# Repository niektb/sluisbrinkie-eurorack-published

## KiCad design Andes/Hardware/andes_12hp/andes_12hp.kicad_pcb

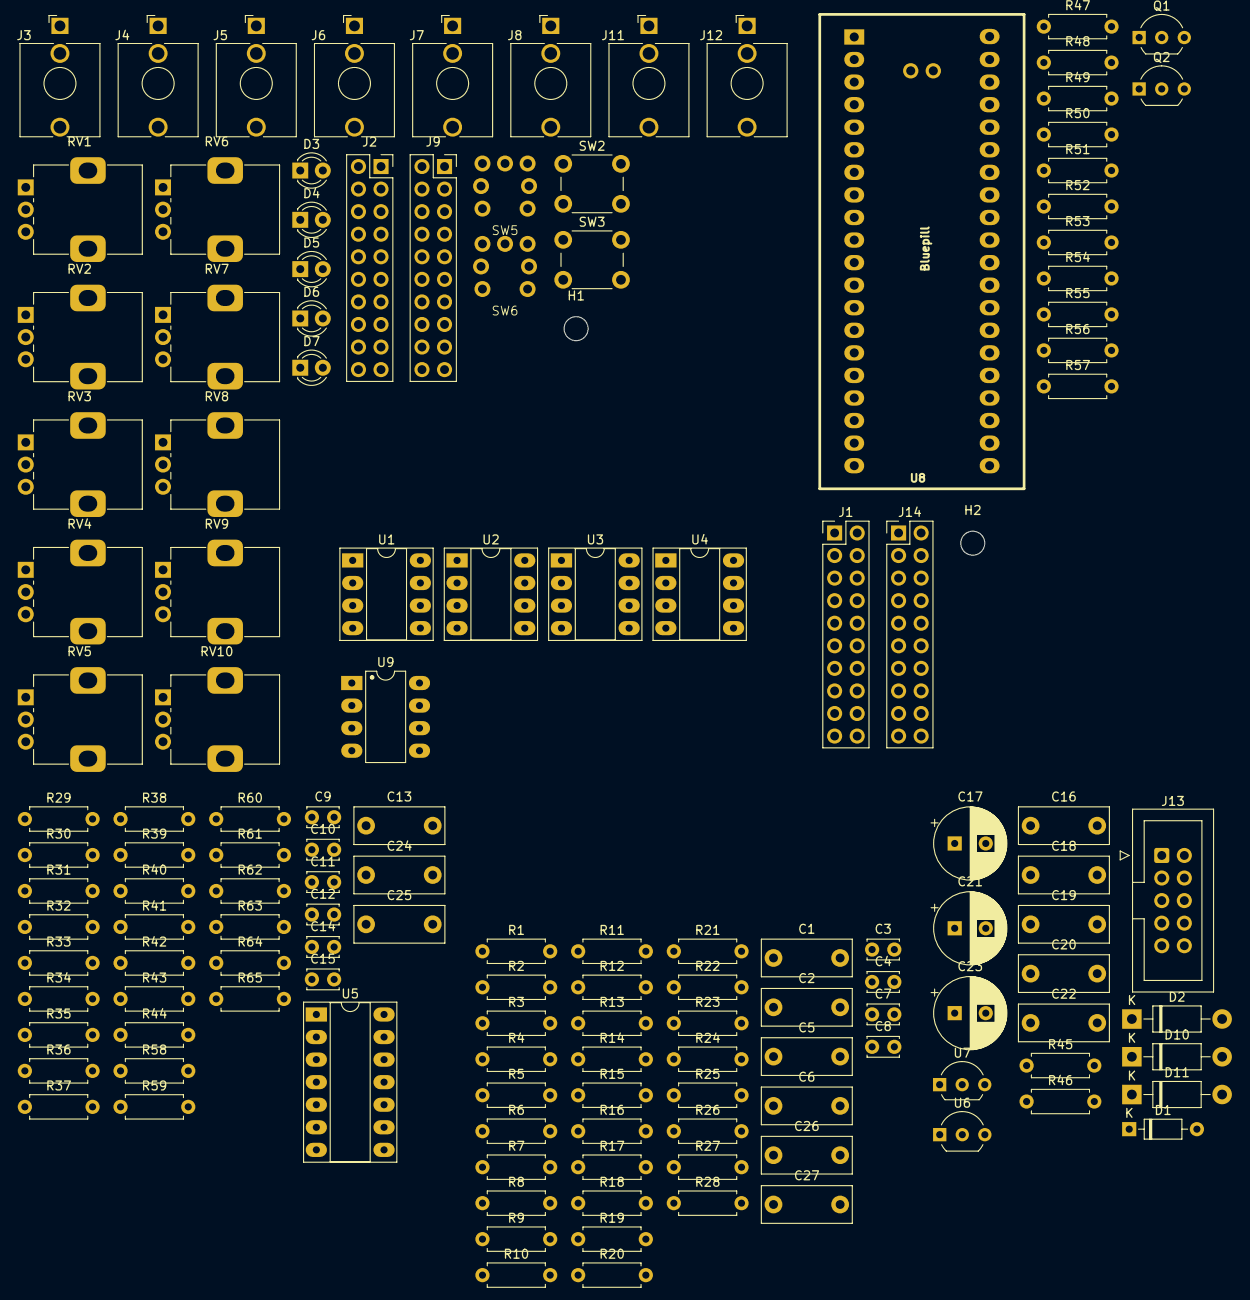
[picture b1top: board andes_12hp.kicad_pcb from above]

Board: 2 copper layers, 141 parts (0 on the bottom side), 118 nets, no tracks yet.

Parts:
C1, C2, C5, C6, C13, C16, C18, C20, C22, C24, C25, C26, C27: 100n; C_Rect_L10.0mm_W4.0mm_P7.50mm_MKS4
C3, C4, C7, C8, C14, C15: 150pf; C_Disc_D3.4mm_W2.1mm_P2.50mm
C9, C10, C11, C12: 4.7n; C_Disc_D3.4mm_W2.1mm_P2.50mm
C17, C21, C23: 10u; CP_Radial_D8.0mm_P3.50mm
C19: 330n; C_Rect_L10.0mm_W4.0mm_P7.50mm_MKS4
D1: BZX55C3V6; D_DO-35_SOD27_P7.62mm_Horizontal
D2, D10, D11: 1N5817; D_DO-41_SOD81_P10.16mm_Horizontal
D3, D4, D5, D6, D7: LED; LED_D3.0mm
H1, H2: MountingHole; MountingHole_2.7mm_M2.5
J1, J14: Pins_02x10_P2.54mm_TH; PinHeader_2x10_P2.54mm_Vertical
J2, J9: Pins_02x10_P2.54mm_TH; PinSocket_2x10_P2.54mm_Vertical
J3: CV1; Jack_3.5mm_QingPu_WQP-PJ398SM_Vertical_CircularHoles_3D
J4: CV2; Jack_3.5mm_QingPu_WQP-PJ398SM_Vertical_CircularHoles_3D
J5: CV3; Jack_3.5mm_QingPu_WQP-PJ398SM_Vertical_CircularHoles_3D
J6: CV4; Jack_3.5mm_QingPu_WQP-PJ398SM_Vertical_CircularHoles_3D
J7: in1; Jack_3.5mm_QingPu_WQP-PJ398SM_Vertical_CircularHoles_3D
J8: in2; Jack_3.5mm_QingPu_WQP-PJ398SM_Vertical_CircularHoles_3D
J11: out1; Jack_3.5mm_QingPu_WQP-PJ398SM_Vertical_CircularHoles_3D
J12: out2; Jack_3.5mm_QingPu_WQP-PJ398SM_Vertical_CircularHoles_3D
J13: Eurorack Power; IDC-Header_2x05_P2.54mm_Vertical
Q1, Q2: 2N3904; TO-92_Inline_Wide
R1, R2, R3, R4, R15, R16, R17, R18, R58, R59, R62, R63: 47k; R_Axial_DIN0207_L6.3mm_D2.5mm_P7.62mm_Horizontal
R5, R6, R7, R8, R9, R10, R11, R12, R19, R20, R21, R22, R23, R24, R25, R26, R56, R57, R60, R61, R64, R65: 100k; R_Axial_DIN0207_L6.3mm_D2.5mm_P7.62mm_Horizontal
R13, R14, R27, R28, R41, R42: 33k; R_Axial_DIN0207_L6.3mm_D2.5mm_P7.62mm_Horizontal
R29, R31, R35, R36, R46: 1k5; R_Axial_DIN0207_L6.3mm_D2.5mm_P7.62mm_Horizontal
R30, R32: 180k; R_Axial_DIN0207_L6.3mm_D2.5mm_P7.62mm_Horizontal
R33, R34: 12k; R_Axial_DIN0207_L6.3mm_D2.5mm_P7.62mm_Horizontal
R37, R39: 15k; R_Axial_DIN0207_L6.3mm_D2.5mm_P7.62mm_Horizontal
R38, R40: 6k8; R_Axial_DIN0207_L6.3mm_D2.5mm_P7.62mm_Horizontal
R43, R44: 1k; R_Axial_DIN0207_L6.3mm_D2.5mm_P7.62mm_Horizontal
R45: 330R; R_Axial_DIN0207_L6.3mm_D2.5mm_P7.62mm_Horizontal
R47, R48, R49, R50, R51, R52, R53: 2k; R_Axial_DIN0207_L6.3mm_D2.5mm_P7.62mm_Horizontal
R54, R55: 10k; R_Axial_DIN0207_L6.3mm_D2.5mm_P7.62mm_Horizontal
RV1, RV2, RV3, RV7: B10k; Potentiometer_Alps_RK09K_Single_Vertical_DSHAFT
RV4, RV5, RV6, RV8, RV9, RV10: B100k; Potentiometer_Alps_RK09K_Single_Vertical
SW2: SW_Dual; SW_PUSH_6mm_H13mm
SW3: SW_Mode; SW_PUSH_6mm_H13mm
SW5, SW6: SW_ML6; ML6-H2T2GQA
U1, U3: TL072CP; DIP-8_W7.62mm_Socket_LongPads
U2, U4: MCP6002-I-P; DIP-8_W7.62mm_Socket_LongPads
U5: TL074CP; DIP-14_W7.62mm_Socket_LongPads
U6: LM4040LP-10; TO-92_Inline_Wide
U7: L78L05_TO92; TO-92L_Inline_Wide
U8: Bluepill; BluePill_STM32F103C
U9: TL072CP; DIP-8_W7.62mm_LongPads

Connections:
+3V3: C2.1, C6.1, R54.1, R55.1, U2.8 (V+), U4.8 (V+), U8.18 (VCC3V3), U8.40 (VCC3V3)
+5V: C18.1, D2.2 (A), U7.1 (VO), U8.38 (5V_USB)
+12V: C1.1, C5.1, C13.1, C19.1, C21.1, C24.1, D2.1 (K), D10.1 (K), U1.8 (V+), U3.8 (V+), U5.4 (V+), U7.3 (VI), U9.8 (V+)
-12V: C16.1, C23.2, C24.2, C25.2, C26.2, C27.2, D11.2 (A), R45.1, R46.2, U1.4 (V-), U3.4 (V-), U5.11 (V-), U9.4 (V-)
/-10V_REF: C17.1, C20.1, J14.4, R45.2, U6.3 (A)
/CV1_ATVPOT: J14.5, R1.2, R2.1, U1.3 (+)
/CV1_JACK: J14.3, R1.1, R5.1
/CV1_POT: J14.7, R10.1
/CV2_ATVPOT: J14.11, R3.2, R4.1, U1.5 (+)
/CV2_JACK: J14.9, R3.1, R6.1
/CV2_POT: J14.13, R12.1
/CV3_ATVPOT: J14.17, R15.2, R16.1, U3.3 (+)
/CV3_JACK: J14.15, R15.1, R19.1
/CV3_POT: J14.18, R24.1
/CV4_ATVPOT: J14.14, R17.2, R18.1, U3.5 (+)
/CV4_JACK: J14.16, R17.1, R20.1
/CV4_POT: J14.12, R26.1
/Front PCB/-10V_REF: J2.4, RV1.3, RV2.3, RV3.3, RV7.3
/Front PCB/CV1_ATVPOT: J2.5, RV4.2
/Front PCB/CV1_JACK: J2.3, J3.T, RV4.1
/Front PCB/CV1_POT: J2.7, RV1.2
/Front PCB/CV2_ATVPOT: J2.11, RV5.2
/Front PCB/CV2_JACK: J2.9, J4.T, RV5.1
/Front PCB/CV2_POT: J2.13, RV2.2
/Front PCB/CV3_ATVPOT: J2.17, RV6.2
/Front PCB/CV3_JACK: J2.15, J5.T, RV6.1
/Front PCB/CV3_POT: J2.18, RV3.2
/Front PCB/CV4_ATVPOT: J2.14, RV8.2
/Front PCB/CV4_JACK: J2.16, J6.T, RV8.1
/Front PCB/CV4_POT: J2.12, RV7.2
/Front PCB/LED1: D3.2 (A), J9.9
/Front PCB/LED2: D4.2 (A), J9.11
/Front PCB/LED3: D5.2 (A), J9.13
/Front PCB/LED4: D6.2 (A), J9.15
/Front PCB/LED5: D7.2 (A), J9.17
/Front PCB/LED_SALIDA_1: J9.5, SW5.L1
/Front PCB/LED_SALIDA_2: J9.7, SW6.L1
/Front PCB/OUT1: J9.18, J11.T
/Front PCB/OUT1_ATVPOT: J9.3, RV9.2
/Front PCB/OUT2: J9.20, J12.T
/Front PCB/OUT2_ATVPOT: J9.4, RV10.2
/Front PCB/PRE_ATV_OUT1: J9.1, RV9.3
/Front PCB/PRE_ATV_OUT2: J9.2, RV10.3
/Front PCB/SW_DUAL: J9.6, SW2.1
/Front PCB/SW_MODE: J9.8, SW3.1
/Front PCB/SW_TRIG1: J9.10, SW5.1, SW5.2
/Front PCB/SW_TRIG2: J9.12, SW6.1, SW6.2
/Front PCB/TRIG_1: J2.8, J7.T
/Front PCB/TRIG_2: J2.10, J8.T
/Inputs/CV1: C3.2, R13.2, U2.1, U8.8 (PA3_RX2)
/Inputs/CV2: C4.2, R14.2, U2.7, U8.7 (PA2_TX2)
/Inputs/CV3: C7.2, R27.2, U4.1, U8.6 (PA1)
/Inputs/CV4: C8.2, R28.2, U4.7, U8.5 (PA0)
/LED1: J1.9, R53.1
/LED2: J1.11, R47.1
/LED3: J1.13, R48.1
/LED4: J1.15, R49.1
/LED5: J1.17, R50.1
/LED_SALIDA_1: J1.5, R52.1
/LED_SALIDA_2: J1.7, R51.1
/OUT1: J1.18, R43.1
/OUT1_ATVPOT: J1.3, R62.2, R63.1, U9.3 (+)
/OUT2: J1.20, R44.1
/OUT2_ATVPOT: J1.4, R58.2, R59.1, U9.5 (+)
/Output/-3V6_REF: C22.1, D1.2 (A), R37.2, R39.2, R46.1
/Output/CH1_PWM1: R29.2, U8.34 (PB6_SCL1)
/Output/CH1_PWM2: R30.2, U8.35 (PB7_SDA1)
/Output/CH2_PWM1: R31.2, U8.36 (PB8)
/Output/CH2_PWM2: R32.2, U8.37 (PB9)
/PRE_ATV_OUT1: C14.2, J1.1, R41.1, R62.1, R64.1, U5.14
/PRE_ATV_OUT2: C15.2, J1.2, R42.1, R58.1, R60.1, U5.1
/Processor/STM_TRIG_1: Q1.3 (C), R54.2, U8.16 (PB11_SDA2)
/Processor/STM_TRIG_2: Q2.3 (C), R55.2, U8.29 (PA12_USBD+)
/SW_DUAL: J1.6, U8.2 (PC13_LED)
/SW_MODE: J1.8, U8.3 (PC14)
/SW_TRIG1: J1.10, U8.25 (PA8)
/SW_TRIG2: J1.12, U8.32 (PB4)
/TRIG_1: J14.8, R56.1
/TRIG_2: J14.10, R57.1
GND: C1.2, C2.2, C5.2, C6.2, C9.2, C10.2, C11.2, C12.2, C13.2, C16.2, C17.2, C18.2, C19.2, C20.2, C21.2, C22.2, C23.1, C25.1, C26.1, C27.1, D1.1 (K), J1.14, J1.16, J1.19, J13.3, J13.4, J13.5, J13.6, J13.7, J13.8, J14.1, J14.2, J14.6, J14.19, J14.20, Q1.1 (E), Q2.1 (E), R2.2, R4.2, R16.2, R18.2, R59.2, R63.2, U2.3 (+), U2.4 (V-), U2.5 (+), U4.3 (+), U4.4 (V-), U4.5 (+), U5.3 (+), U5.12 (+), U6.2 (K), U7.2 (GND), U8.19 (GND), U8.20 (GND), U8.39 (GND)
GND1: D3.1 (K), D4.1 (K), D5.1 (K), D6.1 (K), D7.1 (K), J2.1, J2.2, J2.6, J2.19, J2.20, J3.S, J3.TN, J4.S, J4.TN, J5.S, J5.TN, J6.S, J6.TN, J7.S, J7.TN, J8.S, J8.TN, J9.14, J9.16, J9.19, J11.S, J12.S, RV1.1, RV2.1, RV3.1, RV4.3, RV5.3, RV6.3, RV7.1, RV8.3, RV9.1, RV10.1, SW2.2, SW3.2, SW5.3, SW5.4 (A), SW5.L2, SW6.3, SW6.4 (A), SW6.L2
unnamed: C9.1, R29.1, R33.1, R35.2
unnamed: C10.1, R31.1, R34.1, R36.2
unnamed: D10.2 (A), J13.9, J13.10
unnamed: D11.1 (K), J13.1, J13.2
unnamed: Q1.2 (B), R56.2
unnamed: Q2.2 (B), R57.2
unnamed: R7.2, R9.1, U1.1
unnamed: R8.2, R11.1, U1.7
unnamed: R21.2, R23.1, U3.1
unnamed: R22.2, R25.1, U3.7
unnamed: R30.1, R33.2
unnamed: R32.1, R34.2
unnamed: R43.2, R65.2, U9.1
unnamed: R44.2, R61.2, U9.7
unnamed: R5.2, R7.1, U1.2 (-)
unnamed: R6.2, R8.1, U1.6 (-)
unnamed: C3.1, R9.2, R10.2, R13.1, U2.2 (-)
unnamed: C4.1, R11.2, R12.2, R14.1, U2.6 (-)
unnamed: R19.2, R21.1, U3.2 (-)
unnamed: R20.2, R22.1, U3.6 (-)
unnamed: C7.1, R23.2, R24.2, R27.1, U4.2 (-)
unnamed: C8.1, R25.2, R26.2, R28.1, U4.6 (-)
unnamed: C15.1, R39.1, R40.1, R42.2, U5.2 (-)
unnamed: C12.1, R36.1, U5.5 (+)
unnamed: R40.2, U5.6 (-), U5.7
unnamed: C11.1, R35.1, U5.10 (+)
unnamed: R38.2, U5.8, U5.9 (-)
unnamed: C14.1, R37.1, R38.1, R41.2, U5.13 (-)
unnamed: R47.2, U8.9 (PA4)
unnamed: R48.2, U8.10 (PA5_SCK1)
unnamed: R49.2, U8.11 (PA6_MISO1)
unnamed: R50.2, U8.12 (PA7_MOSI1)
unnamed: R51.2, U8.13 (PB0)
unnamed: R52.2, U8.14 (PB1)
unnamed: R53.2, U8.15 (PB10_SCL2)
unnamed: R64.2, R65.1, U9.2 (-)
unnamed: R60.2, R61.1, U9.6 (-)

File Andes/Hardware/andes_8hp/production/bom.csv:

Designator,Footprint,Quantity,Value,LCSC Part #
"C1, C13, C16, C2, C20, C22, C24, C25, C26, C5, C6",0603,11,100n,
"C10, C11, C12, C9",0603,4,4.7n,
"C14, C15, C3, C4, C7, C8",0603,6,150pf,
"C17, C18, C19, C21, C23",1206,5,22uF,
"D11, D8, D9",D_SOD-123,3,B140HW-7,
DZ1,D_SOD-323,1,ZMM3V6,
J1,PinSocket_2x08_P2.54mm_Vertical,1,Conn_02x08_Odd_Even,
J13,IDC-Header_2x05_P2.54mm_Vertical,1,Eurorack Power,
J14,PinSocket_2x12_P2.54mm_Vertical,1,Conn_02x12_Odd_Even,
"Q1, Q2",SOT-23,2,S8050 J3Y,
"R1, R15, R16, R17, R18, R2, R3, R4, R58, R59, R62, R63",0603,12,47k,
"R10, R11, R12, R19, R20, R21, R22, R23, R24, R25, R26, R5, R56, R57, R6, R60, R61, R64, R65, R7, R8, R9",0603,22,100k,
"R13, R14, R27, R28, R41, R42",0603,6,33k,
"R29, R31, R35, R36",0603,4,1k5,
"R30, R32",0603,2,180k,
"R33, R34",0603,2,12k,
"R37, R39",0603,2,15k,
"R38, R40",0603,2,6k8,
"R43, R44",0603,2,1k,
R45,0603,1,330,
R46,0603,1,1k2,
"R47, R48, R49, R50, R51, R52, R53",0603,7,2k,
"R54, R55",0603,2,10k,
"U1, U3, U9",SO-8_3.9x4.9mm_P1.27mm,3,TL072CD,
"U2, U4",SO-8_3.9x4.9mm_P1.27mm,2,MCP6002-I-SN,
U5,SOIC-14_3.9x8.7mm_P1.27mm,1,TL074CD,
U6,SOT-23,1,LM4040DBZ-10,
U7,SOT-223-3_TabPin2,1,AMS1117-5.0,
U8,BluePill_STM32F103C,1,Bluepill,
